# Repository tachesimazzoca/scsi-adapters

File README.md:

# SCSI Adapters

This repository contains PCB files for SCSI adapters.

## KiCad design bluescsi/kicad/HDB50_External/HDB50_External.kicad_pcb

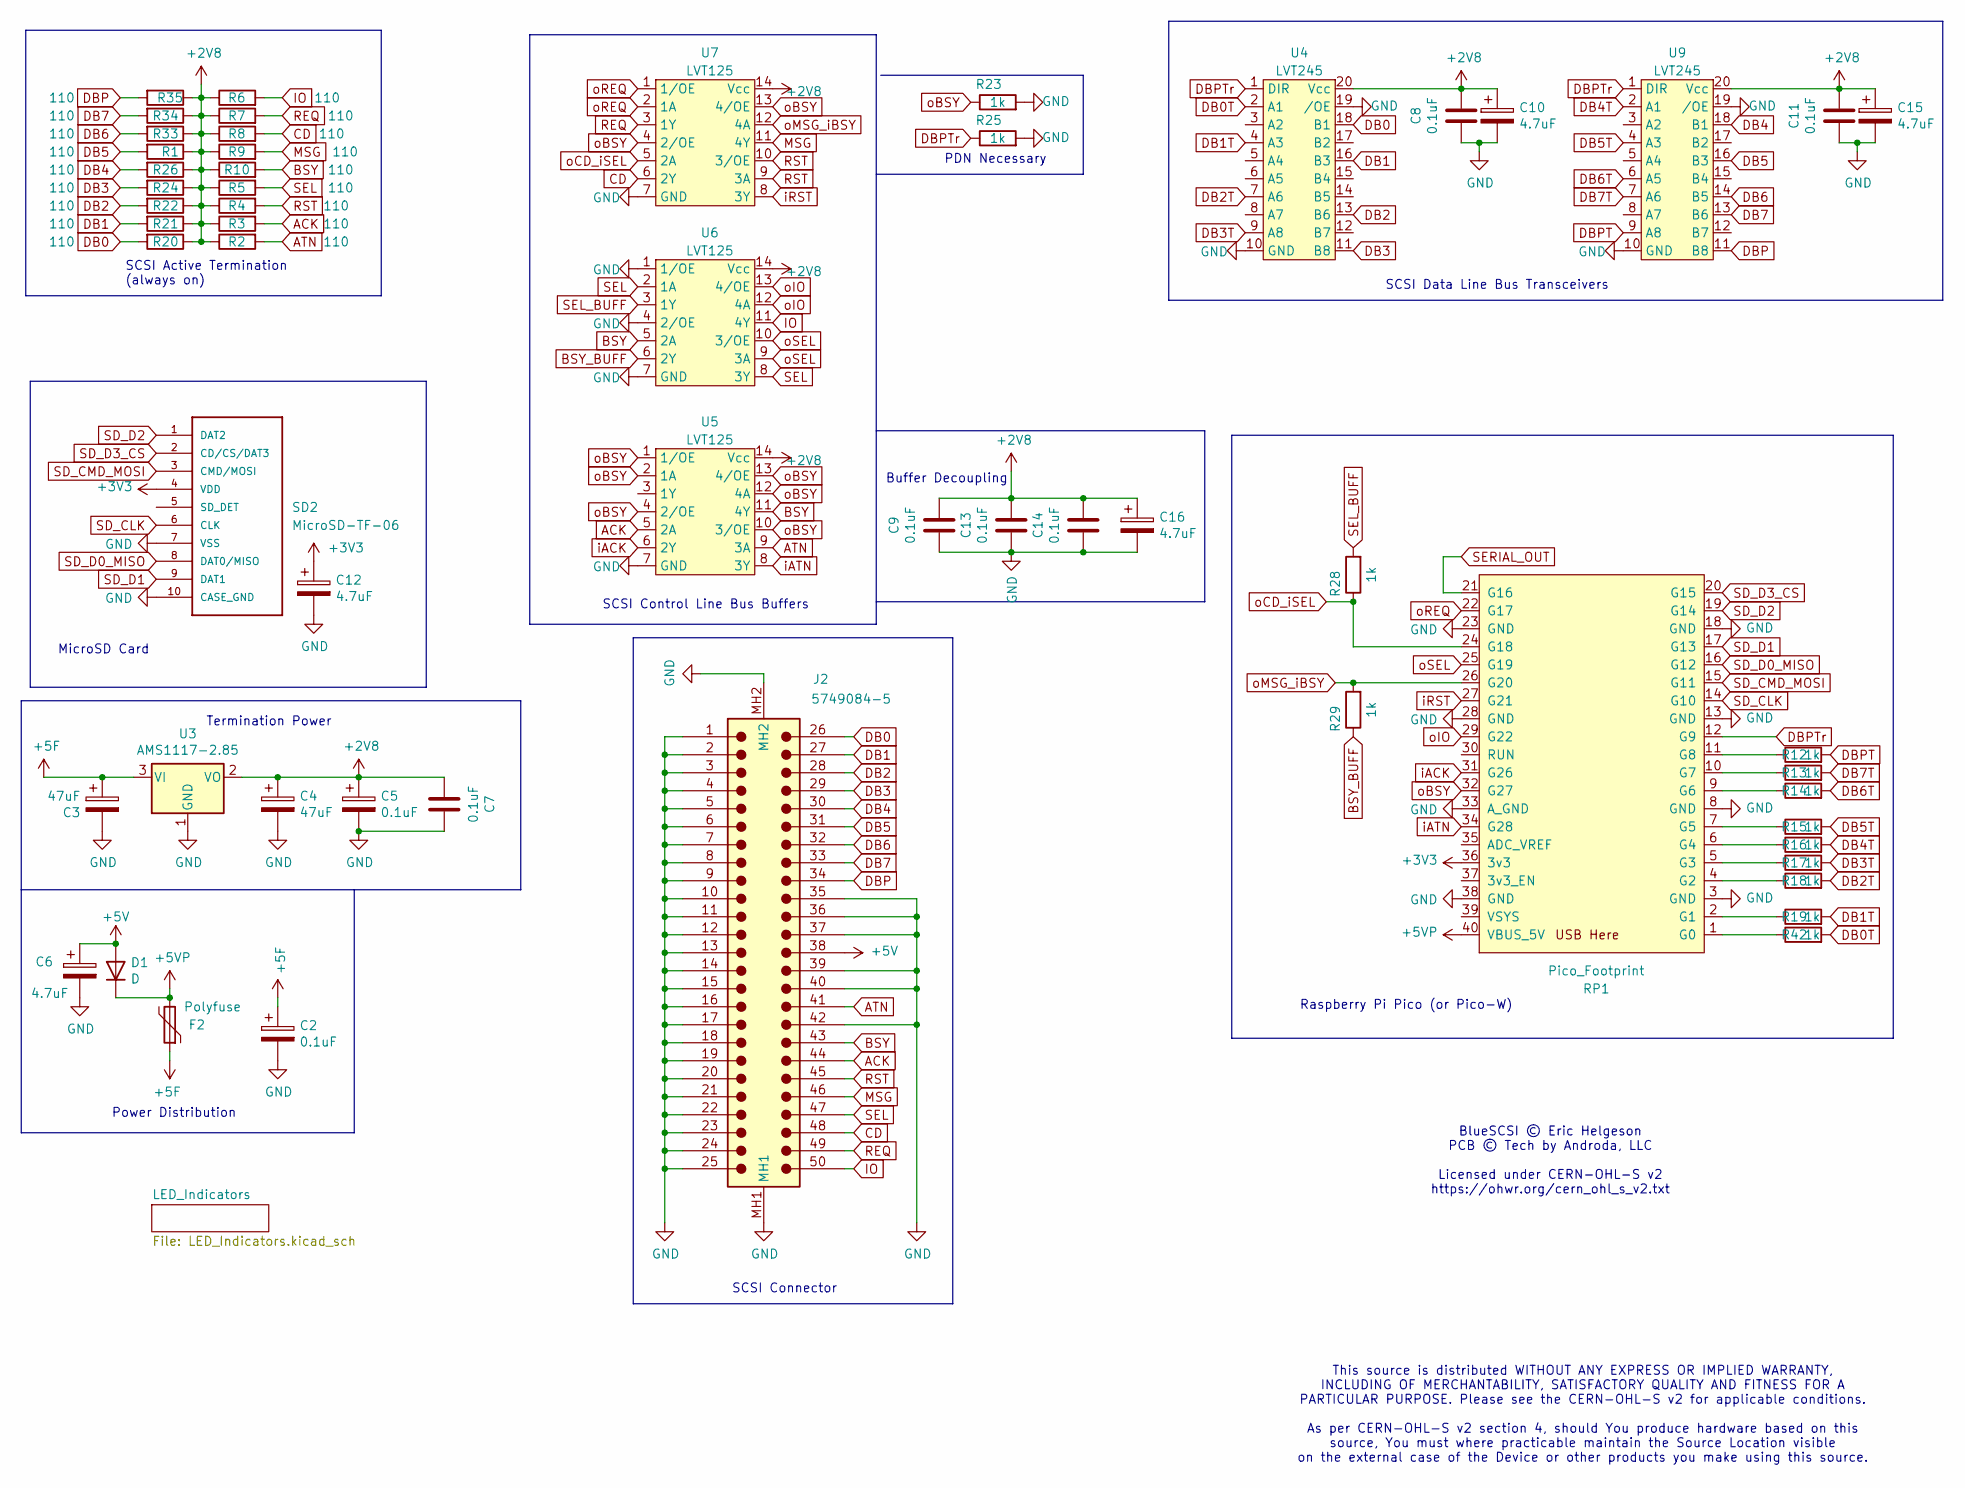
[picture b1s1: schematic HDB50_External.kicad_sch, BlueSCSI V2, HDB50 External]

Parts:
C2, C5, C8, C11: 0.1uF; C_0805_2012Metric_Pad1.15x1.40mm_HandSolder
C3, C4: 47uF; C_1206_3216Metric_Pad1.42x1.75mm_HandSolder
C6, C12: 4.7uF; C_0805_2012Metric_Pad1.15x1.40mm_HandSolder
C7, C9, C13, C14: 0.1uF; C_0603_1608Metric_Pad1.08x0.95mm_HandSolder
C10, C15, C16: 4.7uF; C_0805_2012Metric_Pad1.18x1.45mm_HandSolder
D1: D; D_SMA
F2: Polyfuse; Fuse_0805_2012Metric_Pad1.15x1.40mm_HandSolder
J2: 5749084-5; TE_5749084_5
R1, R2, R3, R4, R5, R6, R7, R8, R9, R10, R20, R21, R22, R24, R26, R33, R34, R35: 110; R_0603_1608Metric_Pad0.98x0.95mm_HandSolder
R12, R13, R14, R15, R16, R17, R18, R19, R23, R25, R28, R29, R42: 1k; R_0603_1608Metric_Pad0.98x0.95mm_HandSolder
RP1: Pico_Footprint; BluePillModule
SD2: MicroSD-TF-06; TF-06_MicroSD; MANUFACTURER_PART_NUMBER C693844
U3: AMS1117-2.85; SOT-223-3_TabPin2
U4, U9: LVT245; TSSOP-20_4.4x6.5mm_P0.65mm
U5, U6, U7: LVT125; TSSOP-14_4.4x5mm_P0.65mm

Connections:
+2V8: C4.1, C5.1, C7.1, C8.1, C9.2, C10.1, C11.1, C13.2, C14.2, C15.1, C16.1, R1.1, R2.1, R3.1, R4.1, R5.1, R6.1, R7.1, R8.1, R9.1, R10.1, R20.1, R21.1, R22.1, R24.1, R26.1, R33.1, R34.1, R35.1, U3.2 (VO), U4.20 (Vcc), U5.14 (Vcc), U6.14 (Vcc), U7.14 (Vcc), U9.20 (Vcc)
+3V3: C12.1, RP1.36 (3v3), SD2.4 (VDD); also elsewhere on the board
+5F: C2.1, C3.1, F2.1, U3.3 (VI); also elsewhere on the board
+5V: C6.1, D1.2 (A), J2.38
+5VP: D1.1 (K), F2.2, RP1.40 (VBUS_5V)
ACK: J2.44, R3.2, U5.5 (2A)
ATN: J2.41, R2.2, U5.9 (3A)
BSY: J2.43, R10.2, U5.11 (4Y), U6.5 (2A)
BSY_BUFF: R29.1, U6.6 (2Y)
CD: J2.48, R8.2, U7.6 (2Y)
DB0: J2.26, R20.2, U4.18 (B1)
DB0T: R42.2, U4.2 (A1)
DB1: J2.27, R21.2, U4.16 (B3)
DB1T: R19.2, U4.4 (A3)
DB2: J2.28, R22.2, U4.13 (B6)
DB2T: R18.2, U4.7 (A6)
DB3: J2.29, R24.2, U4.11 (B8)
DB3T: R17.2, U4.9 (A8)
DB4: J2.30, R26.2, U9.18 (B1)
DB4T: R16.2, U9.2 (A1)
DB5: J2.31, R1.2, U9.16 (B3)
DB5T: R15.2, U9.4 (A3)
DB6: J2.32, R33.2, U9.14 (B5)
DB6T: R14.2, U9.6 (A5)
DB7: J2.33, R34.2, U9.13 (B6)
DB7T: R13.2, U9.7 (A6)
DBP: J2.34, R35.2, U9.11 (B8)
DBPT: R12.2, U9.9 (A8)
DBPTr: R25.1, RP1.12 (G9), U4.1 (DIR), U9.1 (DIR)
GND: C2.2, C3.2, C4.2, C5.2, C6.2, C7.2, C8.2, C9.1, C10.2, C11.2, C12.2, C13.1, C14.1, C15.2, C16.2, J2.1, J2.2, J2.3, J2.4, J2.5, J2.6, J2.7, J2.8, J2.9, J2.10, J2.11, J2.12, J2.13, J2.14, J2.15, J2.16, J2.17, J2.18, J2.19, J2.20, J2.21, J2.22, J2.23, J2.24, J2.25, J2.35, J2.36, J2.37, J2.39, J2.40, J2.42, J2.MH1, J2.MH2, R23.2, R25.2, RP1.3 (GND), RP1.8 (GND), RP1.13 (GND), RP1.18 (GND), RP1.23 (GND), RP1.28 (GND), RP1.33 (A_GND), RP1.38 (GND), SD2.7 (VSS), SD2.10 (CASE_GND), U3.1 (GND), U4.10 (GND), U4.19 (/OE), U5.7 (GND), U6.1 (1/OE), U6.4 (2/OE), U6.7 (GND), U7.7 (GND), U9.10 (GND), U9.19 (/OE); also elsewhere on the board
IO: J2.50, R6.2, U6.11 (4Y)
MSG: J2.46, R9.2, U7.11 (4Y)
unnamed: R42.1, RP1.1 (G0)
unnamed: R19.1, RP1.2 (G1)
unnamed: R18.1, RP1.4 (G2)
unnamed: R17.1, RP1.5 (G3)
unnamed: R16.1, RP1.6 (G4)
unnamed: R15.1, RP1.7 (G5)
unnamed: R14.1, RP1.9 (G6)
unnamed: R13.1, RP1.10 (G7)
unnamed: R12.1, RP1.11 (G8)
REQ: J2.49, R7.2, U7.3 (1Y)
RST: J2.45, R4.2, U7.9 (3A), U7.10 (3/OE)
SD_CLK: RP1.14 (G10), SD2.6 (CLK)
SD_CMD_MOSI: RP1.15 (G11), SD2.3 (CMD/MOSI)
SD_D0_MISO: RP1.16 (G12), SD2.8 (DAT0/MISO)
SD_D1: RP1.17 (G13), SD2.9 (DAT1)
SD_D2: RP1.19 (G14), SD2.1 (DAT2)
SD_D3_CS: RP1.20 (G15), SD2.2 (CD/CS/DAT3)
SEL: J2.47, R5.2, U6.2 (1A), U6.8 (3Y)
SEL_BUFF: R28.2, U6.3 (1Y)
SERIAL_OUT: RP1.21 (G16)
iACK: RP1.31 (G26), U5.6 (2Y)
iATN: RP1.34 (G28), U5.8 (3Y)
iRST: RP1.27 (G21), U7.8 (3Y)
oBSY: R23.1, RP1.32 (G27), U5.1 (1/OE), U5.2 (1A), U5.4 (2/OE), U5.10 (3/OE), U5.12 (4A), U5.13 (4/OE), U7.4 (2/OE), U7.13 (4/OE); also elsewhere on the board
oCD_iSEL: R28.1, RP1.24 (G18), U7.5 (2A)
oIO: RP1.29 (G22), U6.12 (4A), U6.13 (4/OE)
oMSG_iBSY: R29.2, RP1.26 (G20), U7.12 (4A)
oREQ: RP1.22 (G17), U7.1 (1/OE), U7.2 (1A)
oSEL: RP1.25 (G19), U6.9 (3A), U6.10 (3/OE)

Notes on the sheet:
Termination Power
Raspberry Pi Pico (or Pico-W)
MicroSD Card
BlueSCSI © Eric Helgeson PCB © Tech by Androda, LLC Licensed under CERN-OHL-S v2 https://ohwr.org/cern_ohl_s_v2.txt
Power Distribution
SCSI Connector
SCSI Data Line Bus Transceivers
SCSI Control Line Bus Buffers
PDN Necessary
This source is distributed WITHOUT ANY EXPRESS OR IMPLIED WARRANTY, INCLUDING OF MERCHANTABILITY, SATISFACTORY QUALITY AND FITNESS FOR A PARTICULAR PURPOSE. Please see the CERN-OHL-S v2 for applicable conditions. As per CERN-OHL-S v2 section 4, should You produce hardware based on this source, You 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
SCSI Active Termination (always on)
Buffer Decoupling

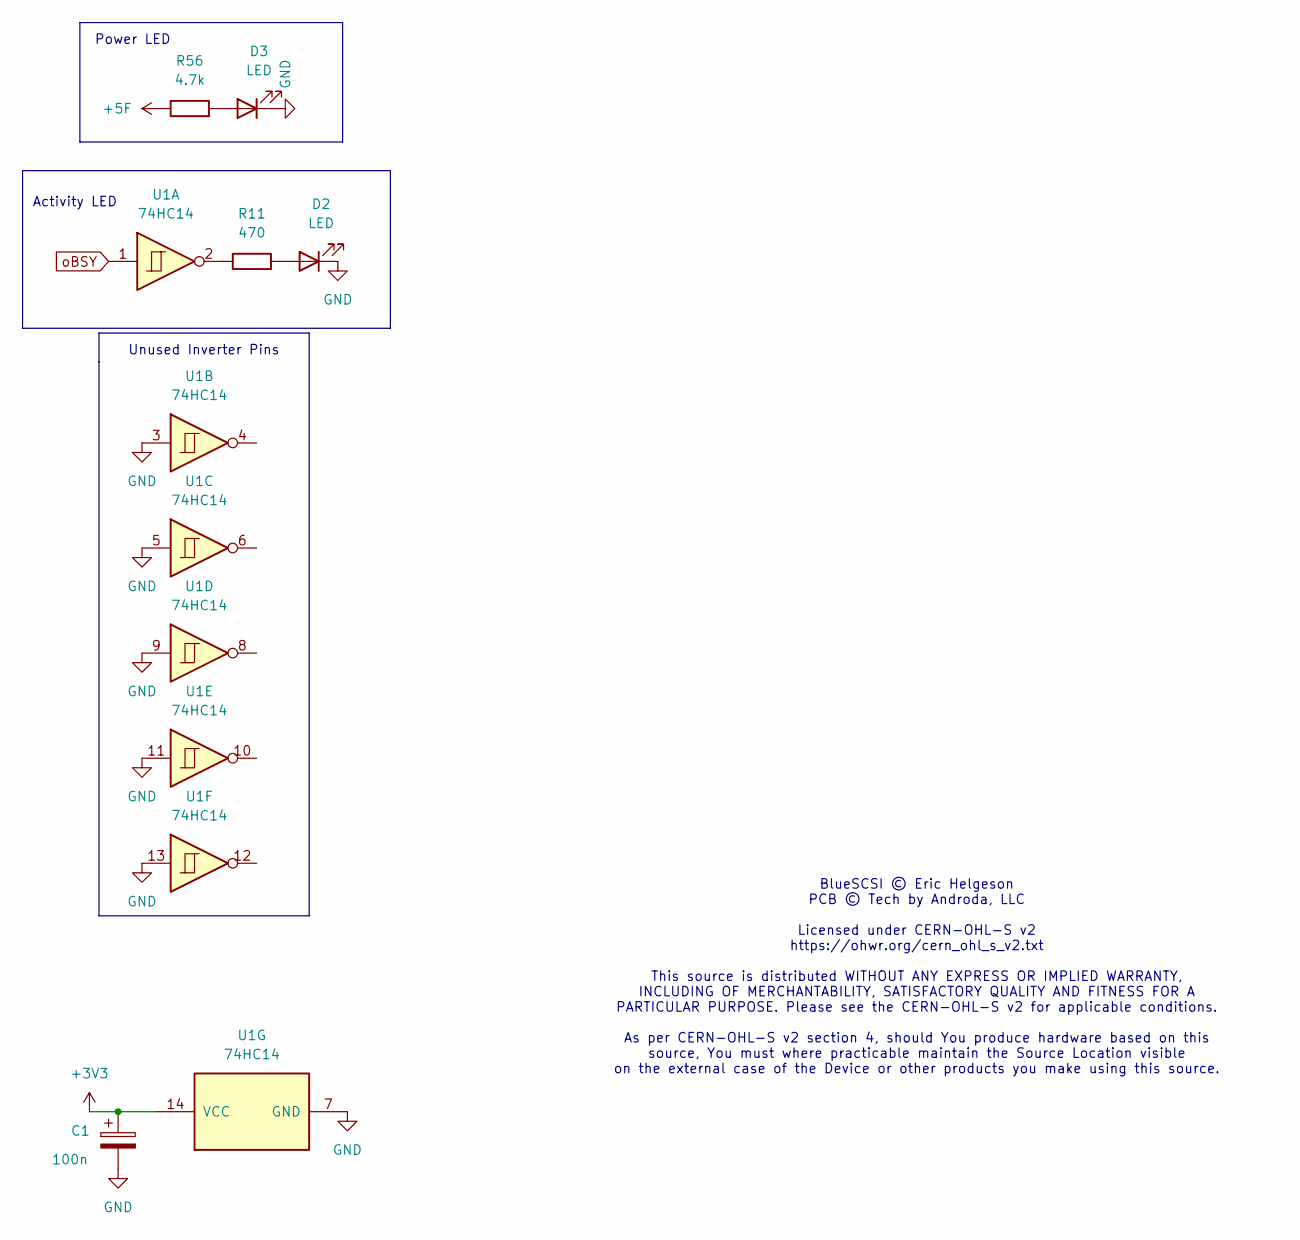
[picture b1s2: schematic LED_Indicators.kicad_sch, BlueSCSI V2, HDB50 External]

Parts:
C1: 100n; C_0805_2012Metric_Pad1.15x1.40mm_HandSolder
D2, D3: LED; LED_0603_1608Metric_Pad1.05x0.95mm_HandSolder
R11: 470; R_0603_1608Metric_Pad0.98x0.95mm_HandSolder
R56: 4.7k; R_0603_1608Metric_Pad0.98x0.95mm_HandSolder
U1: 74HC14

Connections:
+3V3: C1.1, U1.14 (VCC); also elsewhere on the board
+5F: R56.1; also elsewhere on the board
GND: C1.2, D2.1 (K), D3.1 (K), U1.3, U1.5, U1.7 (GND), U1.9, U1.11, U1.13; also elsewhere on the board
unnamed: D2.2 (A), R11.2
unnamed: D3.2 (A), R56.2
unnamed: R11.1, U1.2
oBSY: U1.1; also elsewhere on the board

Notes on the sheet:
Power LED
BlueSCSI © Eric Helgeson PCB © Tech by Androda, LLC Licensed under CERN-OHL-S v2 https://ohwr.org/cern_ohl_s_v2.txt This source is distributed WITHOUT ANY EXPRESS OR IMPLIED WARRANTY, INCLUDING OF MERCHANTABILITY, SATISFACTORY QUALITY AND FITNESS FOR A PARTICULAR PURPOSE. Please see the CERN-OHL-S 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
Activity LED
Unused Inverter Pins

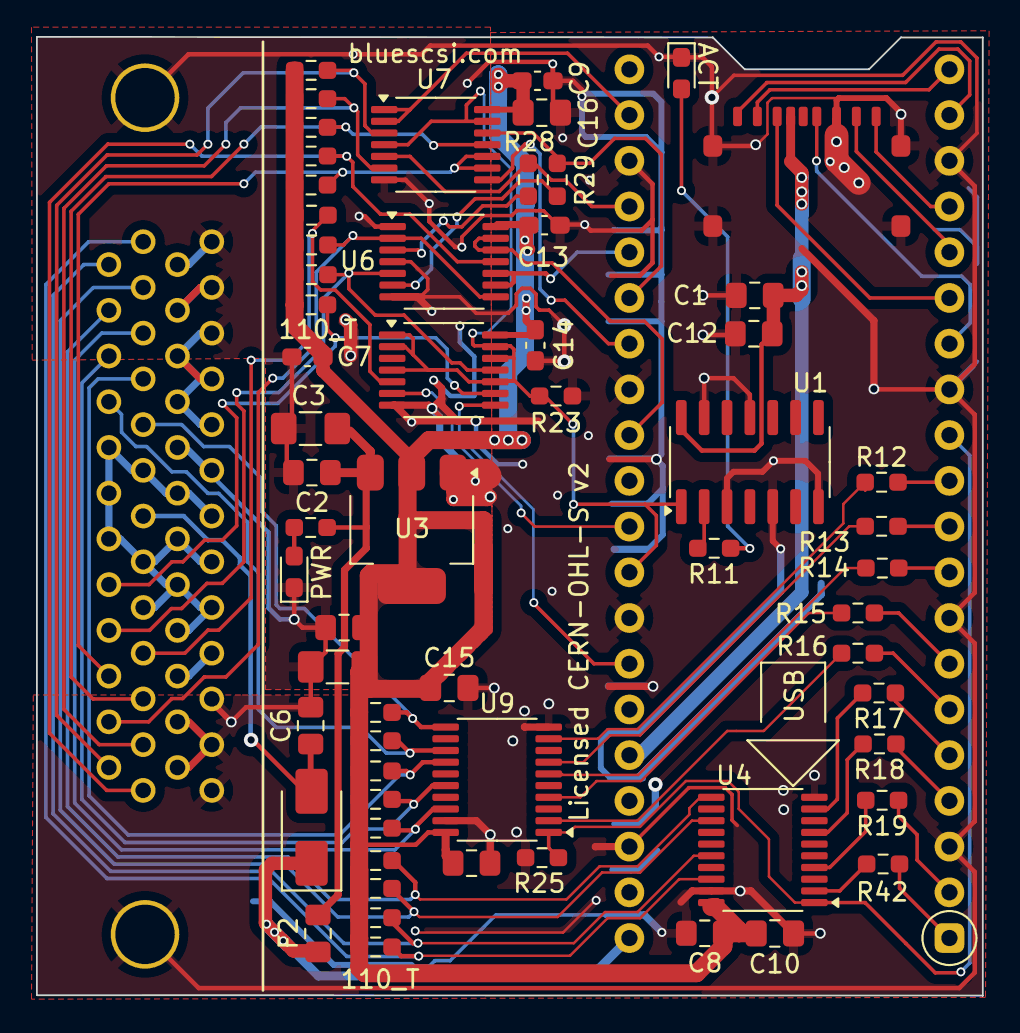
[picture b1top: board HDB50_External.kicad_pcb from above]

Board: 2 copper layers, 52.6 x 53.3 mm, 63 parts (0 on the bottom side), 63 nets.

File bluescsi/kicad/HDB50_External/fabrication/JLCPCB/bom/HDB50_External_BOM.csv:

Comment,Designator,Footprint,LCSC Part #
47uF,"C3,C4",C_1206_3216Metric_Pad1.42x1.75mm_HandSolder,C96123
AMS1117-2.85,U3,SOT-223-3_TabPin2,C2859803
0.1uF,"C1,C2,C5,C8,C11",C_0805_2012Metric_Pad1.15x1.40mm_HandSolder,C28233
4.7uF,"C6,C12,C15,C16,C10",C_0805_2012Metric_Pad1.15x1.40mm_HandSolder,C1779
D,D1,D_SMA,C2480
1k,"R18,R13,R19,R14,R16,R17,R15,R23,R25,R29,R12,R42,R28",R_0603_1608Metric_Pad0.98x0.95mm_HandSolder,C21190
110,"R24,R4,R33,R20,R5,R35,R1,R22,R9,R26,R3,R7,R8,R2,R10,R34,R21,R6",R_0603_1608Metric_Pad0.98x0.95mm_HandSolder,C141676
4.7k,R56,R_0603_1608Metric_Pad0.98x0.95mm_HandSolder,C23162
LED_ACT,D2,LED_0603_1608Metric_Pad1.05x0.95mm_HandSolder,C2986058
LED_PWR,D3,LED_0603_1608Metric_Pad1.05x0.95mm_HandSolder,C2290
LVTH245,"U4,U9",TSSOP-20_4.4x6.5mm_P0.65mm,C2652121
470,R11,R_0603_1608Metric_Pad0.98x0.95mm_HandSolder,C23179
MicroSD-TF-06,SD2,TF-06_MicroSD,C693844
74HC14,U1,SOIC-14_3.9x8.7mm_P1.27mm,C5605
0.1uF,"C13,C7,C14,C9",C_0603_1608Metric_Pad1.08x0.95mm_HandSolder,C14663
LVT125,"U7,U5,U6",TSSOP-14_4.4x5mm_P0.65mm,C7042
Polyfuse,F2,Fuse_0805_2012Metric_Pad1.15x1.40mm_HandSolder,C883111

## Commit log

2025-06-24 Add d25p50k
2025-07-20 Add BlueSCSI HDB50_External
2025-12-21 Add FreeCAD files for BlueSCSI case
    - Define ignore files on repository root
2025-12-29 Add HD50_External.svg
2025-12-29 Add d25p50k/freecad
2025-12-29 Fix DB25 case top margin

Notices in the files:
bluescsi/kicad/HDB50_External/HDB50_External.kicad_pcb:
Licensed CERN-OHL-S v2
